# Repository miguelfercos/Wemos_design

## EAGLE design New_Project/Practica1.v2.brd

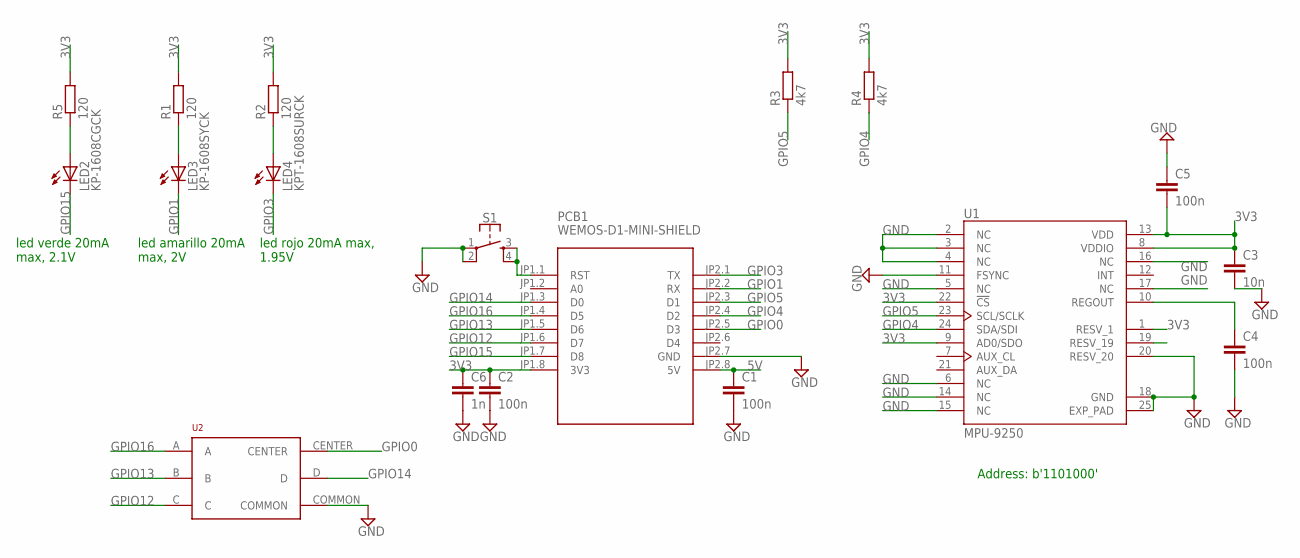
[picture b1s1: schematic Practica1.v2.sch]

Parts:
C1, C2, C4, C5: 100n; C0805
C3: 10n; C0603
C6: 1n; C0402
LED2: KP-1608CGCK; LED_SML0603
LED3: KP-1608SYCK; LED_SML0603
LED4: KPT-1608SURCK; LED_SML0603
PCB1: WEMOS-D1-MINI-SHIELD
R1, R2, R5: 120; R1206
R3, R4: 4k7; R1206
S1: MOMENTARY-SWITCH-SPST-2-SMD-5.2MM-TALL; TACTILE_SWITCH_SMD_5.2MM
U1: MPU-9250; QFN40P300X300X105-25N
U2: JOYSTICK; JOYSTICK_516_316

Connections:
3V3: C2.1, C3.1, C5.2, C6.1, PCB1.JP1.8 (3V3), R1.2, R2.2, R3.2, R4.2, R5.2, U1.1 (RESV_1), U1.8 (VDDIO), U1.9 (AD0/SDO), U1.13 (VDD), U1.22 (!CS)
5V: C1.1, PCB1.JP2.8 (5V)
FEGDC: LED2.A, R5.1
GND: C1.2, C2.2, C3.2, C4.2, C5.1, C6.2, PCB1.JP2.7 (GND), S1.1, S1.2, U1.2 (NC), U1.3 (NC), U1.4 (NC), U1.5 (NC), U1.6 (NC), U1.11 (FSYNC), U1.14 (NC), U1.15 (NC), U1.16 (NC), U1.17 (NC), U1.18 (GND), U1.20 (RESV_20), U1.25 (EXP_PAD), U2.COMMON
GPIO0: PCB1.JP2.5 (D3), U2.CENTER
GPIO1: LED3.C, PCB1.JP2.2 (RX)
GPIO3: LED4.C, PCB1.JP2.1 (TX)
GPIO4: PCB1.JP2.4 (D2), R4.1, U1.24 (SDA/SDI)
GPIO5: PCB1.JP2.3 (D1), R3.1, U1.23 (SCL/SCLK)
GPIO12: PCB1.JP1.6 (D7), U2.C
GPIO13: PCB1.JP1.5 (D6), U2.B
GPIO14: PCB1.JP1.3 (D0), U2.D
GPIO15: LED2.C, PCB1.JP1.7 (D8)
GPIO16: PCB1.JP1.4 (D5), U2.A
unnamed: PCB1.JP1.1 (RST), S1.3, S1.4
unnamed: LED3.A, R1.1
unnamed: LED4.A, R2.1
unnamed: C4.1, U1.10 (REGOUT)

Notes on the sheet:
led verde 20mA max, 2.1V
led amarillo 20mA max, 2V
led rojo 20mA max, 1.95V
Address: b'1101000'

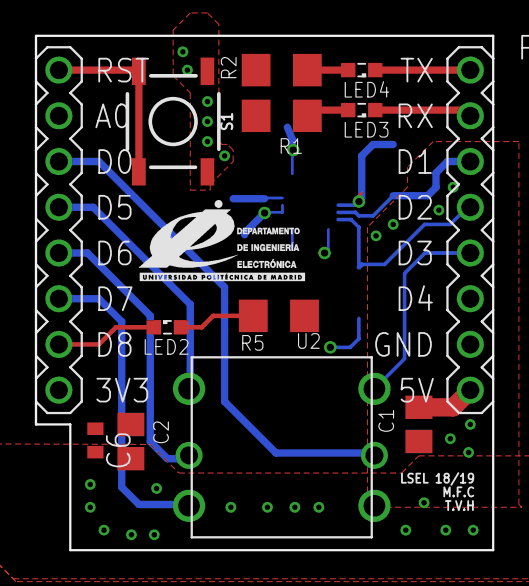
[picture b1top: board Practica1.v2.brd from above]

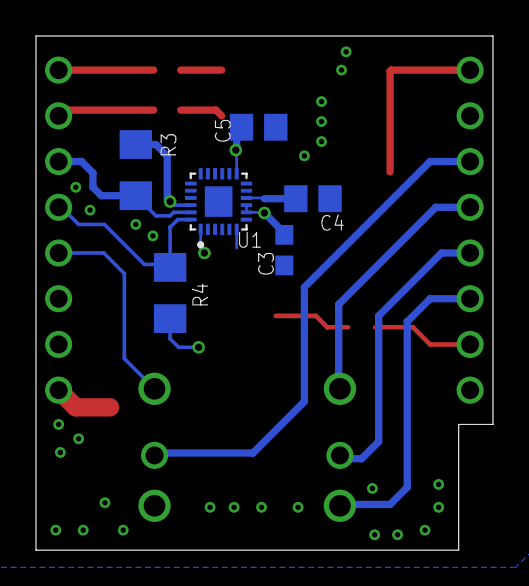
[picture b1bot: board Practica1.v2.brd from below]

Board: 2 copper layers, 25.4 x 28.6 mm, 19 parts (6 on the bottom side), 18 nets.

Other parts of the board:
U$1: DIE_UPM

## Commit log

2023-06-08 uploaded files

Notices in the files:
parts and their libraries:
Shield: Released under the Creative Commons Attribution 4.0 International License: http://creativecommons.org/licenses/by/4.0
SparkFun-Switches: Licensing: Creative Commons ShareAlike 4.0 International - https://creativecommons.org/licenses/by-sa/4.0
